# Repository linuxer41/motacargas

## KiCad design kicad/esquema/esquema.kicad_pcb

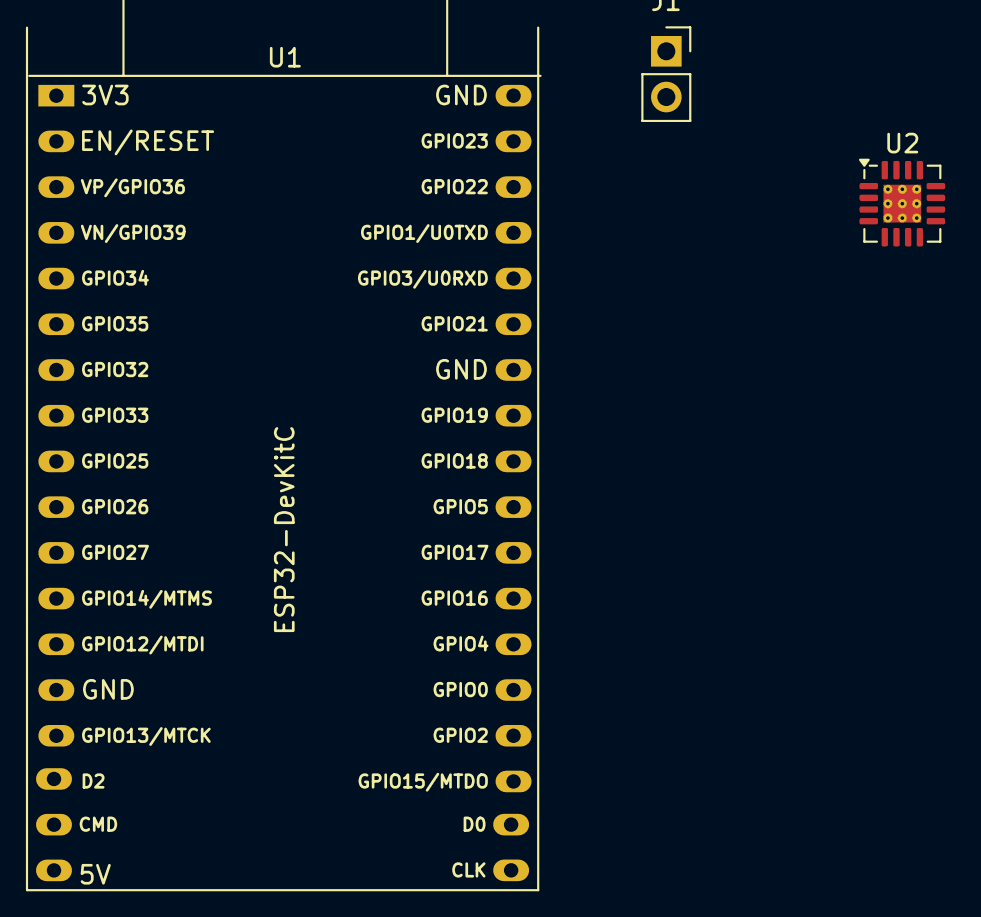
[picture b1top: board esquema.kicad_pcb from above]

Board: 2 copper layers, 3 parts (0 on the bottom side), 2 nets, no tracks yet.

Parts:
J1: Bateria; PinSocket_1x02_P2.54mm_Vertical
U1: ESP32-DevKitC
U2: DRV8833PW; Texas_RTY_WQFN-16-1EP_4x4mm_P0.65mm_EP2.1x2.1mm_ThermalVias

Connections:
+9V: J1.1, U1.19 (5V)
GND: J1.2, U1.14 (GND), U1.32 (GND), U1.38 (GND)

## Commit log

2024-12-17 commit inicial
